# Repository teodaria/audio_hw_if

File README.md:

# hw_dev

This board is designed around AD1983 codec as an expansion board for the STM32MP157C-DK2 evaluation board.
It adds the capability to connect musical intruments to the STM32MP1 and output the processed audio with low latency.

Main features:
 * [AD1983](https://www.analog.com/en/products/ad1983.html) 4 in / 8 out codec
 * [LDLN030](https://www.st.com/en/power-management/ldln030.html) ultra-low noise LDO to generate a clean analog power for the codec and the analog circuitry
 * [TS922](https://www.st.com/content/st_com/en/products/amplifiers-and-comparators/operational-amplifiers-op-amps/automotive-op-amps/ts922.html) low noise audio operational amplifiers
 * 2 input connectors
 * 2 output connectors
 * headphones connector

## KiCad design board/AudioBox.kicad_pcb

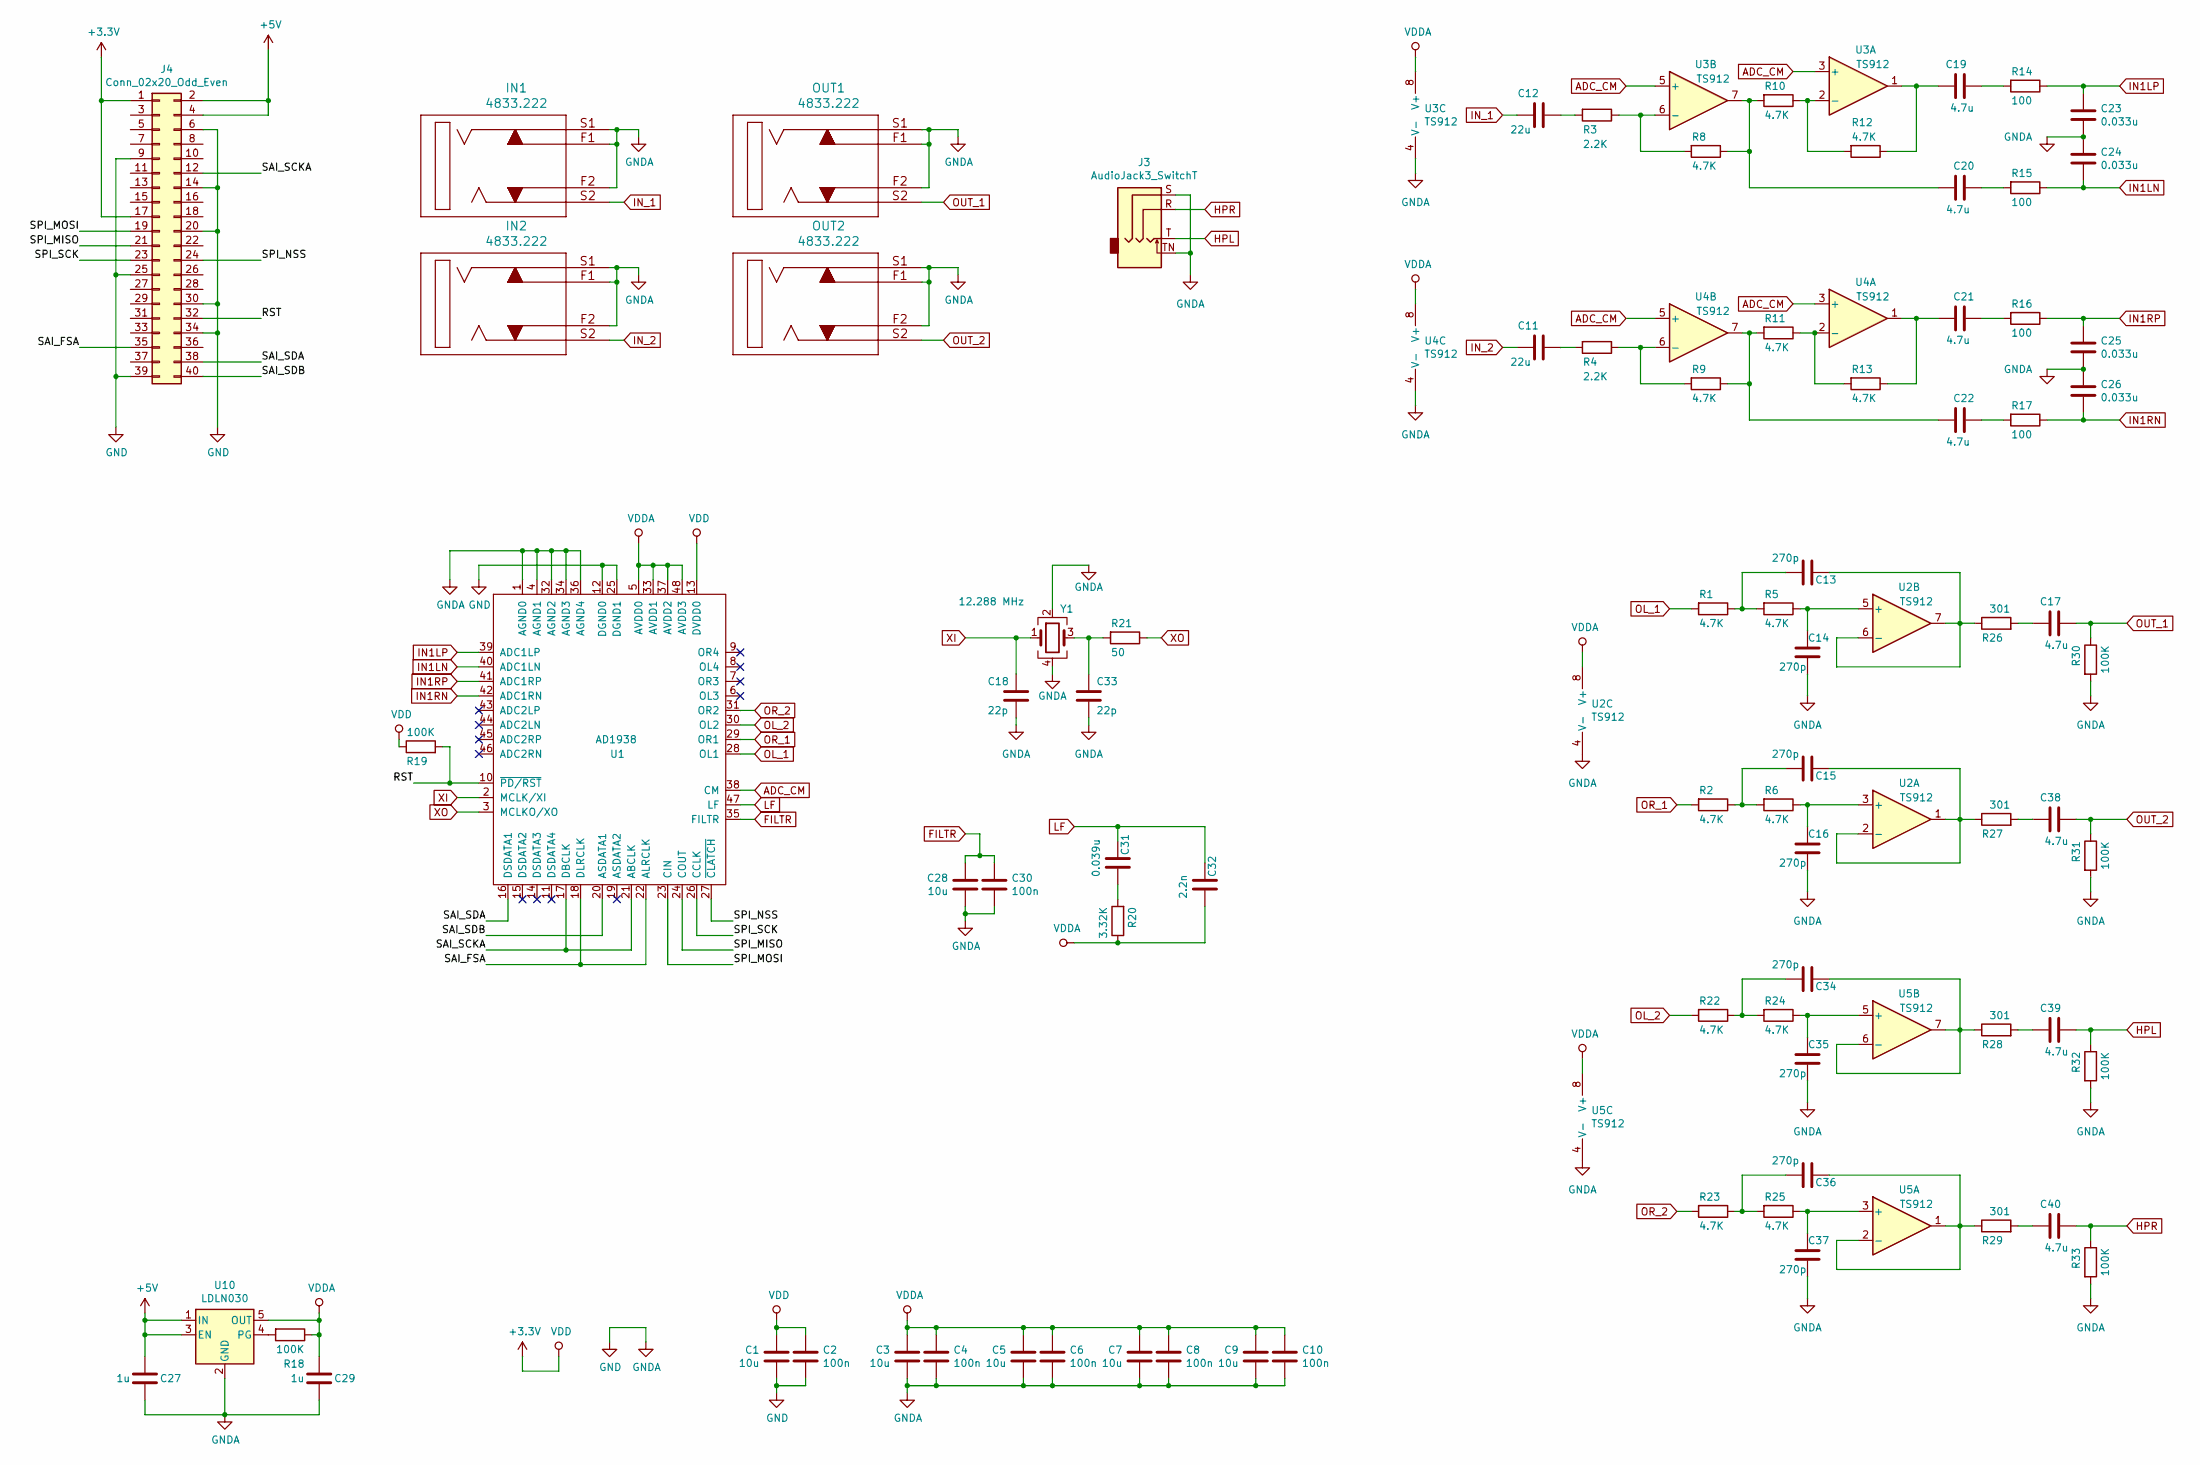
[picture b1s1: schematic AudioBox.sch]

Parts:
C1, C3, C5, C7, C9, C28: 10u; C_0603_1608Metric_Pad1.05x0.95mm_HandSolder; Voltage 25V; Tolerance 10%
C2, C4, C6, C8, C10, C30: 100n; C_0603_1608Metric_Pad1.05x0.95mm_HandSolder; Voltage 25V; Tolerance 10%
C11, C12: 22u; C_0603_1608Metric_Pad1.05x0.95mm_HandSolder; Voltage 10V; Tolerance 20%
C13, C14, C15, C16, C34, C35, C36, C37: 270p; C_0603_1608Metric_Pad1.05x0.95mm_HandSolder; Voltage 100V; Tolerance 1%
C17, C19, C20, C21, C22, C38, C39, C40: 4.7u; C_0603_1608Metric_Pad1.05x0.95mm_HandSolder; Voltage 16V; Tolerance 10%
C18, C33: 22p; C_0603_1608Metric_Pad1.05x0.95mm_HandSolder; Voltage 16V; Tolerance 5%
C23, C24, C25, C26: 0.033u; C_0603_1608Metric_Pad1.05x0.95mm_HandSolder; Voltage 16V; Tolerance 10%
C27, C29: 1u; C_0603_1608Metric_Pad1.05x0.95mm_HandSolder; Voltage 16V; Tolerance 10%
C31: 0.039u; C_0603_1608Metric_Pad1.05x0.95mm_HandSolder; Voltage 50V; Tolerance 10%
C32: 2.2n; C_0603_1608Metric_Pad1.05x0.95mm_HandSolder; Voltage 50V; Tolerance 10%
IN1, IN2: 4833.222
J3: AudioJack3_SwitchT; Jack_3.5mm_CUI_SJ-3524-SMT_Horizontal
J4: Conn_02x20_Odd_Even; PinSocket_2x20_P2.54mm_Vertical
OUT1, OUT2: 4833.222
R1, R2, R5, R6, R8, R9, R10, R11, R12, R13, R22, R23, R24, R25: 4.7K; R_0603_1608Metric_Pad1.05x0.95mm_HandSolder; Tolerance 1%
R3, R4: 2.2K; R_0603_1608Metric_Pad1.05x0.95mm_HandSolder; Tolerance 1%
R14, R15, R16, R17: 100; R_0603_1608Metric_Pad1.05x0.95mm_HandSolder; Tolerance 1%
R18, R19, R30, R31, R32, R33: 100K; R_0603_1608Metric_Pad1.05x0.95mm_HandSolder; Tolerance 5%
R20: 3.32K; R_0603_1608Metric_Pad1.05x0.95mm_HandSolder; Tolerance 1%
R21: 50; R_0603_1608Metric_Pad1.05x0.95mm_HandSolder; Tolerance 1%
R26, R27, R28, R29: 301; R_0603_1608Metric_Pad1.05x0.95mm_HandSolder; Tolerance 1%
U1: AD1938; LQFP-48_7x7mm_P0.5mm
U2, U3, U4, U5: TS912; SO-8_5.3x6.2mm_P1.27mm
U10: LDLN030; SOT-23-5
Y1: 12.288 MHz; Crystal_SMD_Abracon_ABM3B-4Pin_5.0x3.2mm

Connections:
+3V3: C1.2, C2.2, J4.1, J4.17, R19.1, U1.13 (DVDD0)
+5V: C27.2, J4.2, J4.4, U10.1 (IN), U10.3 (EN)
/RST: J4.32, R19.2, U1.10 (~PD/RST)
/SAI_FSA: J4.35, U1.18 (DLRCLK), U1.22 (ALRCLK)
/SAI_SCKA: J4.12, U1.17 (DBCLK), U1.21 (ABCLK)
/SAI_SDA: J4.38, U1.16 (DSDATA1)
/SAI_SDB: J4.40, U1.20 (ASDATA1)
/SPI_MISO: J4.21, U1.24 (COUT)
/SPI_MOSI: J4.19, U1.23 (CIN)
/SPI_NSS: J4.24, U1.27 (~CLATCH)
/SPI_SCK: J4.23, U1.26 (CCLK)
ADC_CM: U1.38 (CM), U3.3 (+), U3.5 (+), U4.3 (+), U4.5 (+)
FILTR: C28.2, C30.2, U1.35 (FILTR)
GND: C1.1, C2.1, C3.1, C4.1, C5.1, C6.1, C7.1, C8.1, C9.1, C10.1, C14.2, C16.2, C18.1, C23.1, C24.2, C25.1, C26.2, C27.1, C28.1, C29.1, C30.1, C33.1, C35.2, C37.2, IN1.F1, IN1.F2, IN1.S1, IN2.F1, IN2.F2, IN2.S1, J3.S, J3.TN, J4.6, J4.9, J4.14, J4.20, J4.25, J4.30, J4.34, J4.39, OUT1.F1, OUT1.F2, OUT1.S1, OUT2.F1, OUT2.F2, OUT2.S1, R30.2, R31.2, R32.2, R33.2, U1.1 (AGND0), U1.4 (AGND1), U1.12 (DGND0), U1.25 (DGND1), U1.32 (AGND2), U1.34 (AGND3), U1.36 (AGND4), U2.4 (V-), U3.4 (V-), U4.4 (V-), U5.4 (V-), U10.2 (GND), Y1.2, Y1.4
HPL: C39.1, J3.T, R32.1
HPR: C40.1, J3.R, R33.1
IN1LN: C24.1, R15.1, U1.40 (ADC1LN)
IN1LP: C23.2, R14.1, U1.39 (ADC1LP)
IN1RN: C26.1, R17.1, U1.42 (ADC1RN)
IN1RP: C25.2, R16.1, U1.41 (ADC1RP)
IN_1: C12.2, IN1.S2
IN_2: C11.2, IN2.S2
LF: C31.1, C32.1, U1.47 (LF)
unnamed: C11.1, R4.2
unnamed: C12.1, R3.2
unnamed: C13.1, R26.1, U2.6 (-), U2.7
unnamed: C13.2, R1.1, R5.2
unnamed: C14.1, R5.1, U2.5 (+)
unnamed: C15.1, R27.1, U2.1, U2.2 (-)
unnamed: C15.2, R2.1, R6.2
unnamed: C16.1, R6.1, U2.3 (+)
unnamed: C17.2, R26.2
unnamed: C19.1, R14.2
unnamed: C19.2, R12.1, U3.1
unnamed: C20.1, R8.1, R10.2, U3.7
unnamed: C20.2, R15.2
unnamed: C21.1, R13.1, U4.1
unnamed: C21.2, R16.2
unnamed: C22.1, R9.1, R11.2, U4.7
unnamed: C22.2, R17.2
unnamed: C31.2, R20.2
unnamed: C33.2, R21.2, Y1.3
unnamed: C34.1, R28.1, U5.6 (-), U5.7
unnamed: C34.2, R22.1, R24.2
unnamed: C35.1, R24.1, U5.5 (+)
unnamed: C36.1, R29.1, U5.1, U5.2 (-)
unnamed: C36.2, R23.1, R25.2
unnamed: C37.1, R25.1, U5.3 (+)
unnamed: C38.2, R27.2
unnamed: C39.2, R28.2
unnamed: C40.2, R29.2
unnamed: R3.1, R8.2, U3.6 (-)
unnamed: R4.1, R9.2, U4.6 (-)
unnamed: R10.1, R12.2, U3.2 (-)
unnamed: R11.1, R13.2, U4.2 (-)
unnamed: R18.2, U10.4 (PG)
OL_1: R1.2, U1.28 (OL1)
OL_2: R22.2, U1.30 (OL2)
OR_1: R2.2, U1.29 (OR1)
OR_2: R23.2, U1.31 (OR2)
OUT_1: C17.1, OUT1.S2, R30.1
OUT_2: C38.1, OUT2.S2, R31.1
VDDA: C3.2, C4.2, C5.2, C6.2, C7.2, C8.2, C9.2, C10.2, C29.2, C32.2, R18.1, R20.1, U1.5 (AVDD0), U1.33 (AVDD1), U1.37 (AVDD2), U1.48 (AVDD3), U2.8 (V+), U3.8 (V+), U4.8 (V+), U5.8 (V+), U10.5 (OUT)
XI: C18.2, U1.2 (MCLK/XI), Y1.1
XO: R21.1, U1.3 (MCLKO/XO)

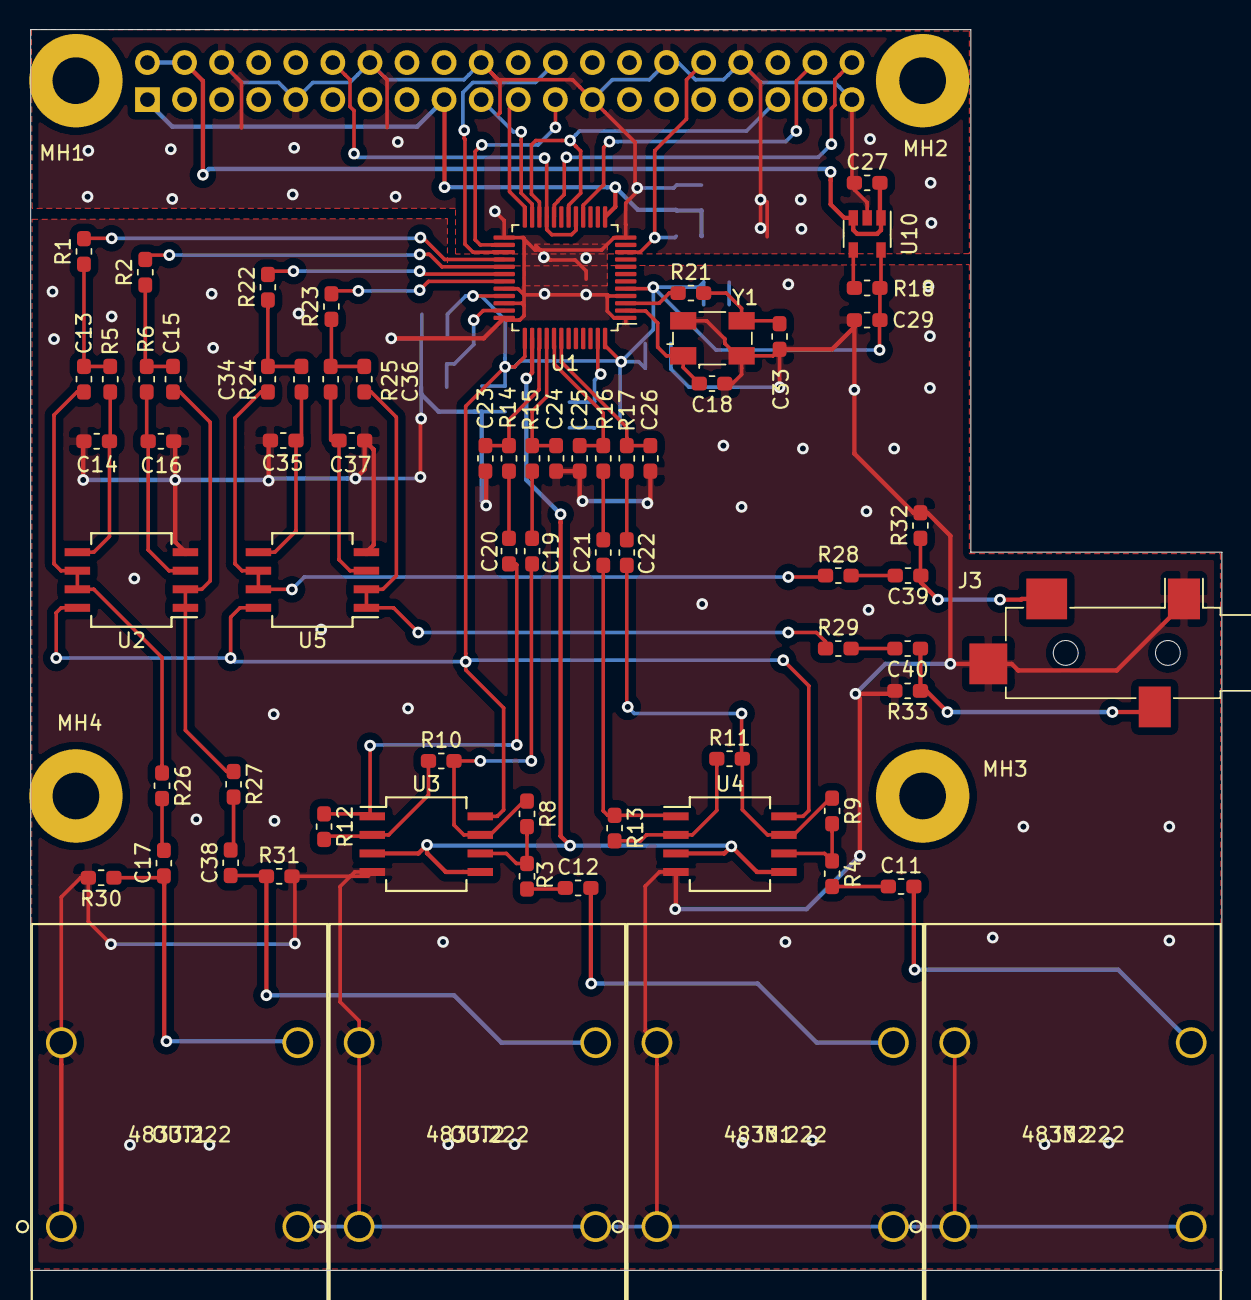
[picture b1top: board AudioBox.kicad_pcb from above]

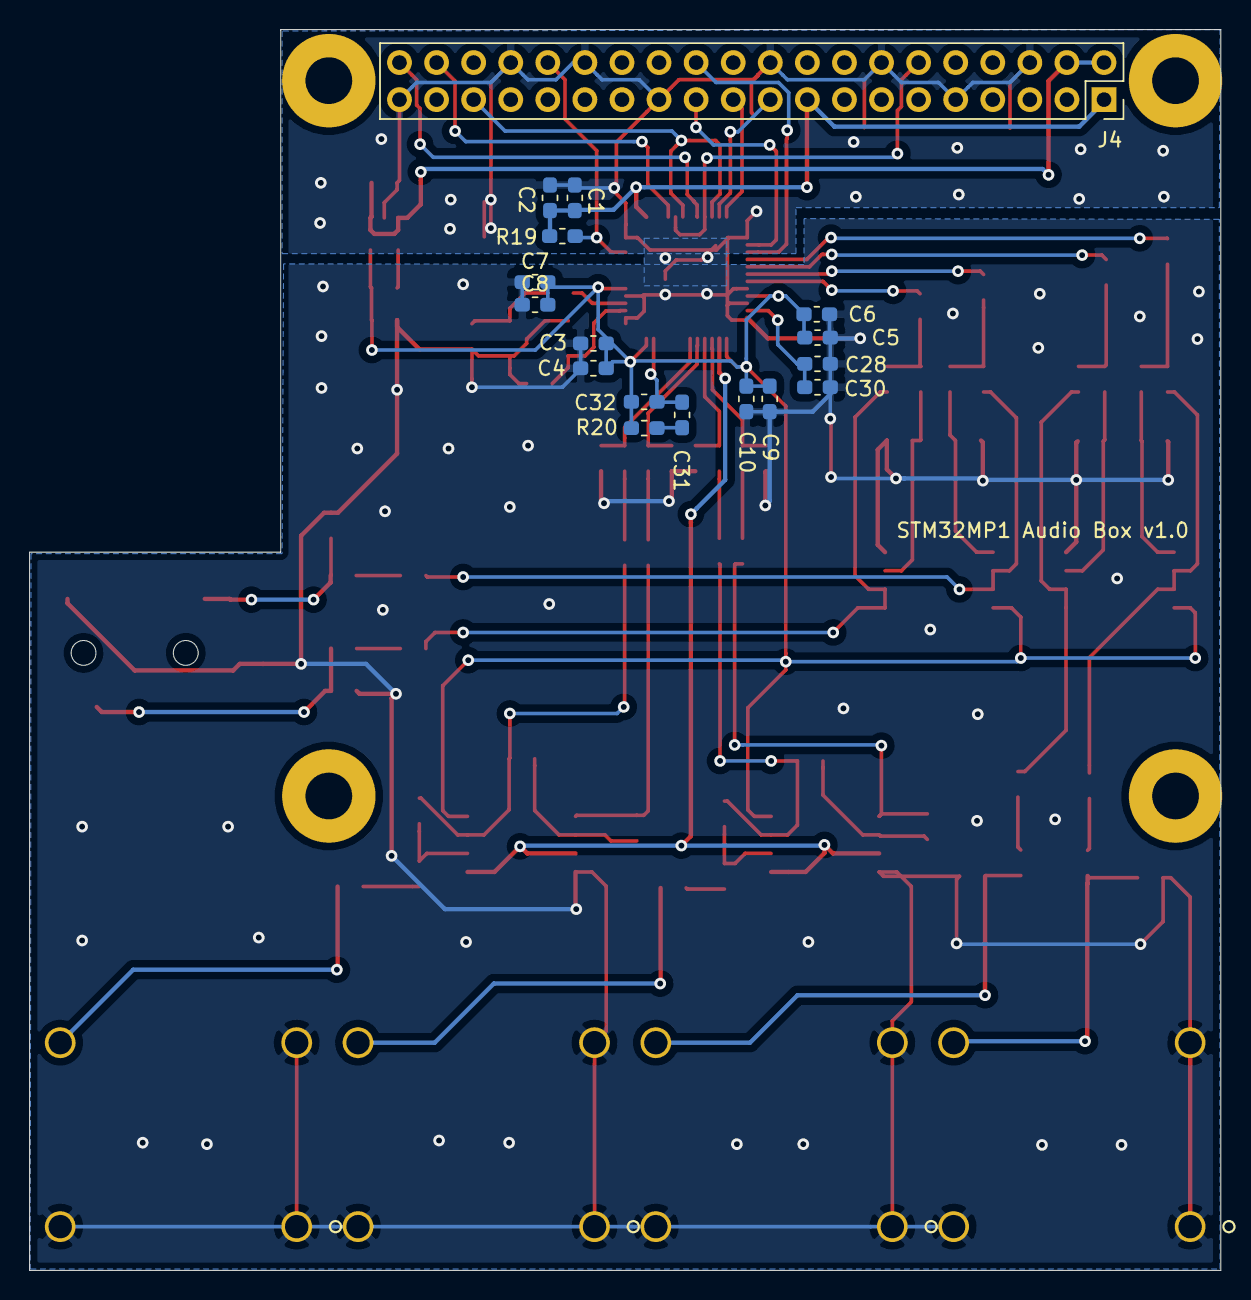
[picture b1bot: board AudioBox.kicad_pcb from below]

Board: 2 copper layers, 81.6 x 85.0 mm, 89 parts (17 on the bottom side), 65 nets.

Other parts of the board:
MH1, MH2, MH3, MH4: MountingHole_3.2mm_M3_Pad

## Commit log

2020-08-20 First dev version
2020-08-22 add custom symbols in the project tree
2020-08-27 half placement done
2020-08-28 finished routing. Silkskreen to do
2020-08-29 updated silkscreen
2020-08-29 minor and generate Gerber
2020-10-24 modified resistor values of the input buffer

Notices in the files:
parts and their libraries:
Copyright 2016 Accelerated Designs. All rights reserved.
